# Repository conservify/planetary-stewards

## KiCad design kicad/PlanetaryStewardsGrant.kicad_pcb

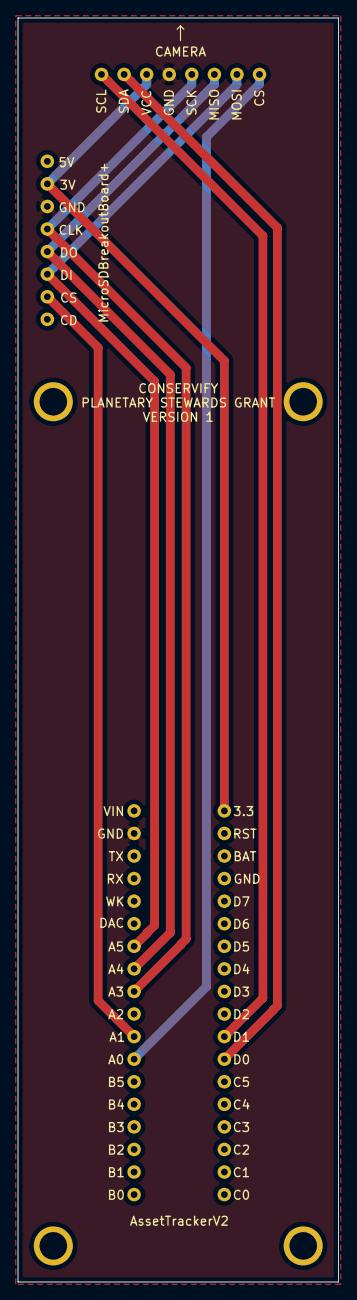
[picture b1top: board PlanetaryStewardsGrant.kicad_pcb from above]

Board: 2 copper layers, 36.1 x 142.2 mm, 3 parts (0 on the bottom side), 9 nets.

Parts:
uArduCam1: Arducam_OV5642
uAssetTracker1: AssetTrackerV2
uSD1: MicroSDBreakoutBoard+

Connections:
+3V3: uArduCam1.6, uAssetTracker1.19, uSD1.2
/CS_ARDU: uArduCam1.1, uAssetTracker1.12
/CS_SD: uAssetTracker1.11, uSD1.7
/MISO: uArduCam1.3, uAssetTracker1.8, uSD1.5
/MOSI: uArduCam1.2, uAssetTracker1.7, uSD1.6
/SCK: uArduCam1.4, uAssetTracker1.9, uSD1.4
/SCL: uArduCam1.8, uAssetTracker1.29
/SDA: uArduCam1.7, uAssetTracker1.30
GND: uArduCam1.5, uAssetTracker1.2, uSD1.3

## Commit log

2019-08-15 Initial commit including KiCad and Particle project files.
2019-08-15 Initial commit including all KiCad and Particle project files.
2019-08-15 Cleaned up files.
